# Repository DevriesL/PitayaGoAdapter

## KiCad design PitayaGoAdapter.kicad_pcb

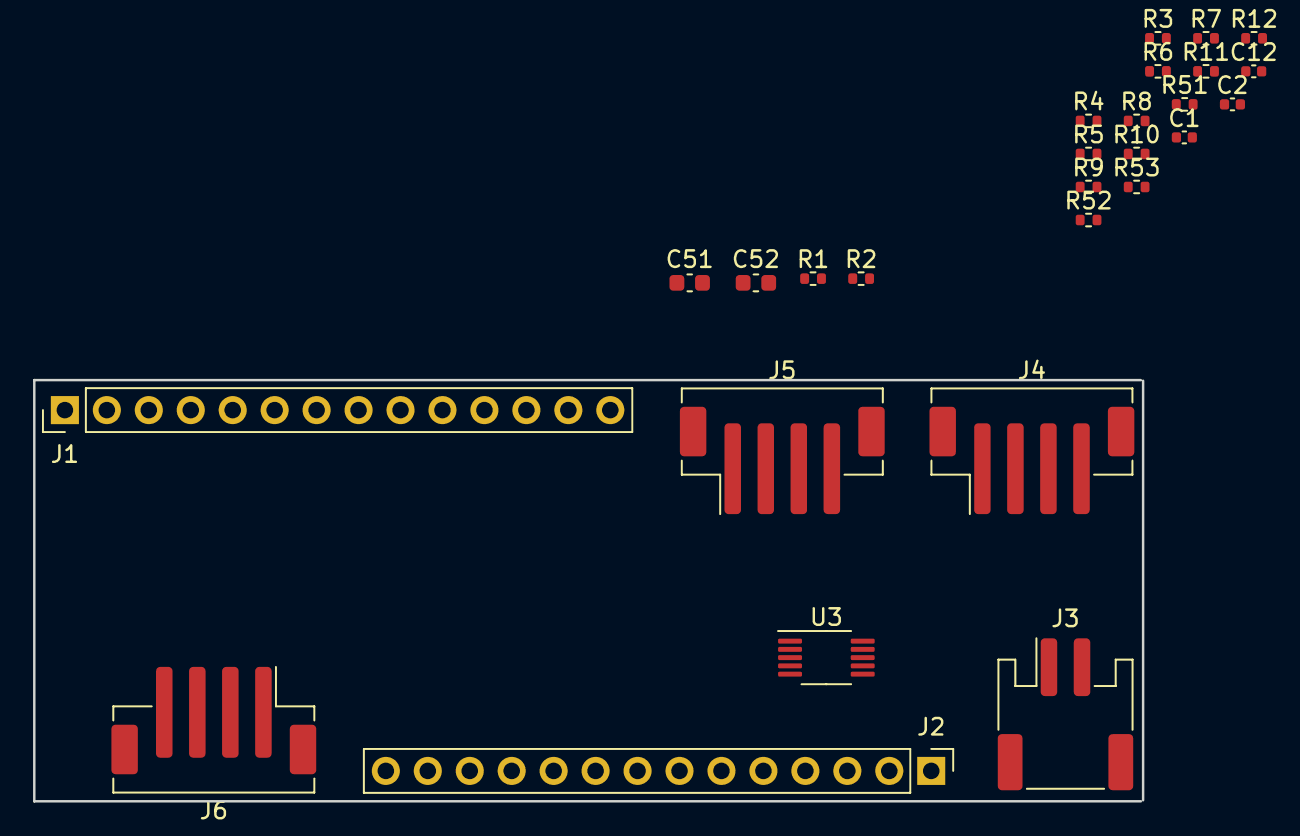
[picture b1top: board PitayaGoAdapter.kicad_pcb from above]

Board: 2 copper layers, 67.1 x 25.5 mm, 27 parts (0 on the bottom side), 21 nets, no tracks yet.

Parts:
C1, C2, C12: 47pF; C_0402_1005Metric
C51, C52: 1uF; C_0603_1608Metric
J1, J2: Conn_01x14; PinHeader_1x14_P2.54mm_Vertical
J3: HAPTIC_Conn; JST_PH_S2B-PH-SM4-TB_1x02-1MP_P2.00mm_Horizontal
J4: HMI_Conn_0_2; JST_PH_B4B-PH-SM4-TB_1x04-1MP_P2.00mm_Vertical
J5: HMI_Conn_3_5; JST_PH_B4B-PH-SM4-TB_1x04-1MP_P2.00mm_Vertical
J6: HMI_Conn_6_8; JST_PH_B4B-PH-SM4-TB_1x04-1MP_P2.00mm_Vertical
R1, R2, R3, R53: 10K; R_0402_1005Metric
R4, R5, R6: 0R; R_0402_1005Metric
R7, R8, R9: 4.3K; R_0402_1005Metric
R10, R11, R12: 24K; R_0402_1005Metric
R51, R52: 2.2K; R_0402_1005Metric
U3: DRV2605LDGS; VSSOP-10_3x3mm_P0.5mm

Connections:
/MB_3V3: J1.1, R1.1, R2.1, R3.1
/MB_4V4: C51.2, J2.13, R51.1, R52.1, R53.1, U3.6, U3.10
/P0.03: C12.1, J1.14, R1.2, R4.2, R7.2, R10.2
/P0.04: C1.1, J1.13, R2.2, R5.2, R8.2, R11.2
/P0.05: C2.1, J1.12, R3.2, R6.2, R9.2, R12.2
/P0.26: J1.7, R51.2, U3.3
/P0.27: J1.6, R52.2, U3.2
GND: C1.2, C2.2, C12.2, C51.1, C52.2, J1.2, J2.12, J3.MP, J4.4, J4.MP, J5.4, J5.MP, J6.4, J6.MP, U3.4, U3.8
unnamed: C52.1, U3.1
unnamed: J3.1, U3.7
unnamed: J3.2, U3.9
unnamed: J4.1, R4.1
unnamed: J4.2, R7.1
unnamed: J4.3, R10.1
unnamed: J5.1, R5.1
unnamed: J5.2, R8.1
unnamed: J5.3, R11.1
unnamed: J6.1, R6.1
unnamed: J6.2, R9.1
unnamed: J6.3, R12.1
unnamed: R53.2, U3.5

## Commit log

2021-11-18 Init project
2021-12-03 Add main board connector
2021-12-03 Update sch and pcb
